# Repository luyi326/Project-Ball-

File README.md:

Project-Ball-
=============

*LOL*

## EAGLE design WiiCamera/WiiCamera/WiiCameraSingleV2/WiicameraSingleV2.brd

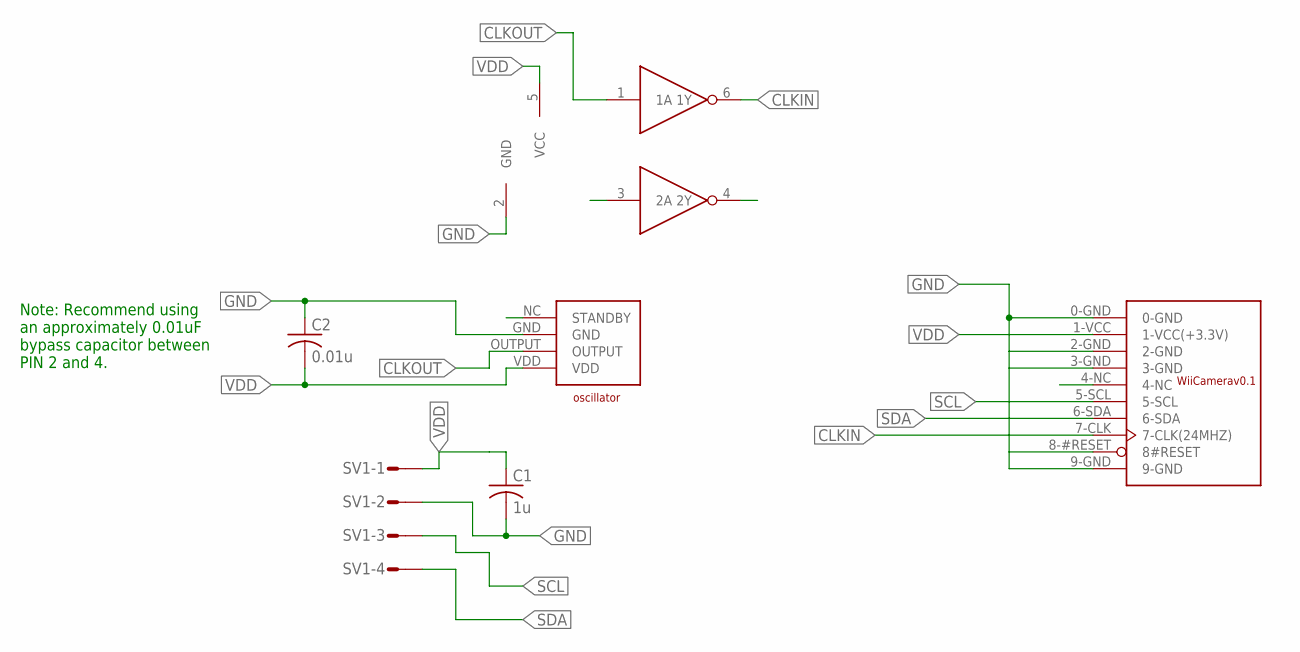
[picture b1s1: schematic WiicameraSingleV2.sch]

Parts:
C1: 1u; C0805
C2: 0.01u; C0805
DUALINV1: SN74LVC2G04
OSC1: OSCILLATOR4-SMD
SV1: S04P
WII1: WIICAMERA

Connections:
CLKIN: DUALINV1.6 (1Y), WII1.7-CLK (7-CLK(24MHZ))
CLKOUT: DUALINV1.1 (1A), OSC1.OUTPUT
GND: C1.2, C2.1, DUALINV1.2 (GND), OSC1.GND, SV1.2, WII1.0-GND, WII1.2-GND, WII1.3-GND, WII1.8-#RESET (8#RESET), WII1.9-GND
SCL: SV1.3, WII1.5-SCL
SDA: SV1.4, WII1.6-SDA
VDD: C1.1, C2.2, DUALINV1.5 (VCC), OSC1.VDD, SV1.1, WII1.1-VCC (1-VCC(+3.3V))

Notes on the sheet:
Note: Recommend using an approximately 0.01uF bypass capacitor between PIN 2 and 4.

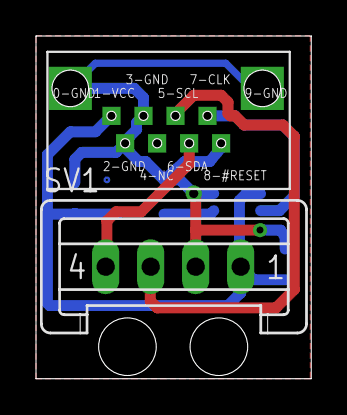
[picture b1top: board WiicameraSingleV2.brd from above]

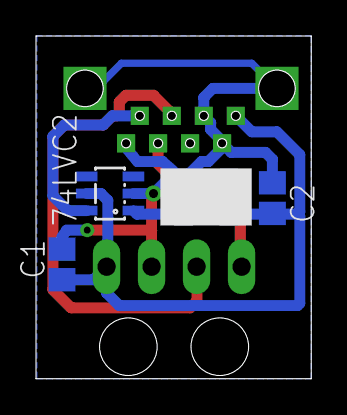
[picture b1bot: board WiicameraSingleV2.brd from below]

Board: 2 copper layers, 15.3 x 19.0 mm, 6 parts (4 on the bottom side), 6 nets.

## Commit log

2014-04-23 Semi working motor control
2014-04-24 first prototype of controlling program
2014-12-19 Initial gitignore
2014-12-19 added a including test file
2014-12-19 add older test file in this ditrectory for reference
2014-12-19 change pwm period from nanosecond to microsecond in order to output detectable waveform
2014-12-19 added blacklib into this directory
2014-12-19 added blacklib in this directory
2014-12-19 added pinout
2014-12-19 new git tools test
2014-12-19 create new pwm port on M2B
2014-12-19 use old function
2014-12-19 test file uploaded. changing frequency possible
2014-12-19 Changed BlackLib directory to obj file and headers
2014-12-19 Updated makefile
2014-12-19 Modified test
2014-12-20 First amendment for stepper motor driver (Not tested)
2014-12-20 Test program for motor
2014-12-21 More test code and fix some cimpilation error.
2014-12-21 First try of BlackStepper
2014-12-21 Fixed some compilation and syntax bug
2014-12-21 Added Acceleration for BlackStepper
2014-12-22 added device tree and adafruit lib for gpio defining
2014-12-22 More testing code and modified BlackStepper to use freq
2014-12-22 added a boneDebiceTree repo
2014-12-22 Fixed issues in numerous direction and speed related problems
2014-12-22 Added debugging information and switch
2014-12-22 added tested pin overlay
2014-12-22 added build shell script
2014-12-22 Remove some comment and added preliminary code for motor pair
2014-12-22 Preliminary PVision Port (Not tested)
2014-12-22 Dual motor first test
2014-12-22 lalala
2014-12-22 modify build
2014-12-22 modify dts file
2014-12-22 use example from exploringbbb
2014-12-22 Added timing to dualstepper
2014-12-22 added new overlay file to enable pwm0a on GPIO_2 at P9_22
2014-12-22 fuxk u overlay
2014-12-24 Switch I2C bus to native I2C handler
2014-12-25 Modified PVision lib
2014-12-25 Temp change to dual motor
2014-12-26 Fixed syntax error in PVision
2014-12-26 added datasheet folder
2014-12-26 Added exploringBB reference
2014-12-26 added archieved photo of wii controller board
2014-12-28 Modified source code and added debugging information
2014-12-28 Added rim skeleton
2014-12-28 Joystick working but not pretty Zzz...
2014-12-29 Added some new functions to PVision and IRRim
2015-01-07 Changed some constants
2015-01-07 Test ctrl-c handler
2015-01-07 Added sigint handler in all stepper testing cases
2015-01-07 revive pinout
2015-01-11 Fix minor bug on direction
2015-01-13 Initial sensor drivers (HMC5883L not implemented)
2015-01-13 Initial test program for sensors
2015-01-13 Fixed syntax error in sensor code
2015-01-17 3rd party sensor drivers (not tested)
2015-01-25 Jan 25 update
2015-01-25 added some new file including eagle libraries
2015-01-27 Some failed test codes
2015-01-30 upload naughtyball board
2015-01-30 UART overlay
2015-01-30 Remove uart overlay
2015-01-30 upload L3G4200D
2015-01-30 modified ADXL345
2015-02-05 daily commit
2015-02-05 Delete BeagleBoardPinoutP8.pdf
    no pdf
2015-02-05 Delete BeagleBoardPinoutP9.pdf
    no pdf
2015-02-05 Delete am3359.pdf
    no pdf
2015-02-05 Delete GPIOs on the Beaglebone Black using the Device Tree Overlays _ derekmolloy.pdf
    pdf
2015-02-05 Delete 3D_CVM_CVM_3-644896-4_G.pdf
    no pdf
2015-02-05 Delete ENG_CD_171825_Y2_171825-c.pdf
    no pdf
2015-02-05 Delete ENG_CD_644893_G_baseFilename.pdf
    no pdf
2015-02-05 Delete ENG_CD_644896_H_baseFilename.pdf
    no pdf
2015-02-05 Delete L3G4200D.pdf
    no pdf
2015-02-05 Delete LM339.pdf
    no pdf
2015-02-05 Delete cdc5801a_CLKGenerator.pdf
    no pdf
2015-02-05 Delete tca9544a_4CHI2C.pdf
    no pdf
2015-02-05 Delete tca9548a_8CHI2C.pdf
    no pdf
2015-02-05 Delete ukw1979_e.pdf
    no pdf
2015-02-05 renew gitignore, no pdf
2015-02-05 use uart1 is good
2015-02-06 First attempt on turn
2015-02-06 Tony's UART receiver test
2015-02-06 Fix Makefile
2015-02-06 finish controller driver/sender. begin to decode
2015-02-06 stepper turning
2015-02-06 Test main
2015-02-06 xcommand finished
2015-02-08 Added variable acceleration step
2015-02-11 wii camera update
2015-02-11 First commit for mux
2015-02-11 begin to simulate
2015-02-11 finish 555 design part
2015-02-11 Change some code in IR
2015-02-11 Working mux
2015-02-12 timing test
2015-02-12 Added reset to Mux
2015-02-12 Correct turn bias algo
2015-02-12 Set turn bias in dual Motor
2015-02-12 lalalablackServo
2015-02-12 Just some style fix
2015-02-13 Some change to test remote
2015-02-13 no message
2015-02-13 Fix problems in BlackServo
2015-02-15 Change motor turning with bias percentage
2015-02-15 Fix compile issue
2015-02-15 Turning complete?
2015-02-15 Update joystick for updated turning
2015-02-21 finish node lite
2015-02-24 mux working again?
2015-02-24 First test attempt servo + IR
2015-02-24 finish new band node
2015-02-24 Fix compilation issues
2015-02-24 More update on rim seeking algo
2015-02-24 work on 9axis
2015-02-25 update on renew interval
2015-02-27 More update
2015-02-27 Update on grace stop
2015-02-27 Gracefully stop
2015-02-27 demo code
2015-03-04 Kinda working IR? still bad
2015-03-07 More update on IR
2015-03-08 positioning first commit
2015-03-08 Basic ir positioning working, result is scaled, need further inspection
2015-03-09 servo with ADC and calibration
2015-03-09 More update on servo feedbacl
2015-03-11 Servo with feedback working?
2015-03-15 IRRim update for new servo code
2015-03-15 Fix compilation issues in IRRim after BlackServo feedback update
2015-03-31 new code for IRAssemble after feedback is added
2015-04-01 Fix some bug in IR_READ
2015-04-01 working code IRRim
2015-04-01 Expanding scan range
2015-04-01 PID working
2015-04-01 Fix some style
2015-04-01 motor spin
2015-04-01 Fix issue in malformed avg
2015-04-02 Some update on PID
2015-04-02 More update on PID
2015-04-02 Instead of sleep, have IRRim run 5 times in a loop
2015-04-03 tracking working
2015-04-03 more update on tracing
2015-04-04 More update irrim, fix returning last seen target
2015-04-07 Update on intergration
2015-04-09 Some update on stepper
2015-04-09 Fix some issue in tracking and added PID control to turning to target
2015-04-10 matching access addition (not active)
2015-04-12 servo duty precent change for new metal servo
2015-04-16 Precompile commit of legitify the stepper
2015-04-16 terminal-inspect working new blackStepper
2015-04-16 Stepper with bias fixed, ready for test
2015-04-16 minor numerical change
2015-04-17 add reversing and more detailed log
2015-04-17 Semi working now
2015-04-17 tuned code
2015-04-17 update on new program
2015-04-17 Make code in main nicer
2015-04-17 rectify I2CBase
2015-04-18 Another tune for main
2015-04-18 More legifity
2015-04-18 new IR test
2015-04-18 Revert "new IR test"
    This reverts commit e2c82603ed01914a414530f3a5df5e300d46ada9.
2015-04-18 added reversing (not not difference)
2015-04-18 Commit before correcting IRRIm
2015-04-18 new target tracing
2015-04-24 finish current job
2015-04-27 added kalman filter submodule
2015-05-02 Kalman filter + SPI comm + arduino Kalman done
2015-05-05 ADC i2c driver (not tested)
2015-05-05 finish shield2GEN
2015-05-06 Updated arduino related code
2015-05-10 Update on Kalman filter
2015-05-13 ADC semi done
2015-05-13 Dual motor semi done
2015-05-14 stepper PID halfway (sometimes has freezing bug)
2015-05-14 stepper IR done?
2015-05-16 more commit for new code
2015-05-17 Working code Maker Faire
2015-05-18 Calibrated ground level.
2015-05-21 initial pages commit
2015-05-22 test page
2015-05-22 test image
2015-05-22 More test
2015-05-22 some style and stuff
2015-05-22 test new BlackStepper
2015-05-22 bug fix to blackStepper
2015-05-22 Linear speed and acceleration calculation
2015-05-25 update some stuff
